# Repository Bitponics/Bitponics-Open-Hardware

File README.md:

### Hardware
- Bitponics board
- [FTDI adapter](http://www.amazon.com/FTDI-Basic-Breakout-5V/dp/B0068QKQEA/ref=sr_1_5?ie=UTF8&qid=1372819998&sr=8-5&keywords=ftdi)
- Mini USB cable

### Software
- [Arduino 1.0.1](http://arduino.cc/en/Main/Software)
- [FTDI driver](http://www.ftdichip.com/Drivers/VCP.htm)

### Setup
- Copy all directories from `./libraries` into your Arduino's global `libraries` folder. (Usually ~/Documents/Arduino/libraries)
- Open Bitponics code in Arduino
- Set board to "Arduino 2560"
- Set serial your usb serial port
- upload firmware

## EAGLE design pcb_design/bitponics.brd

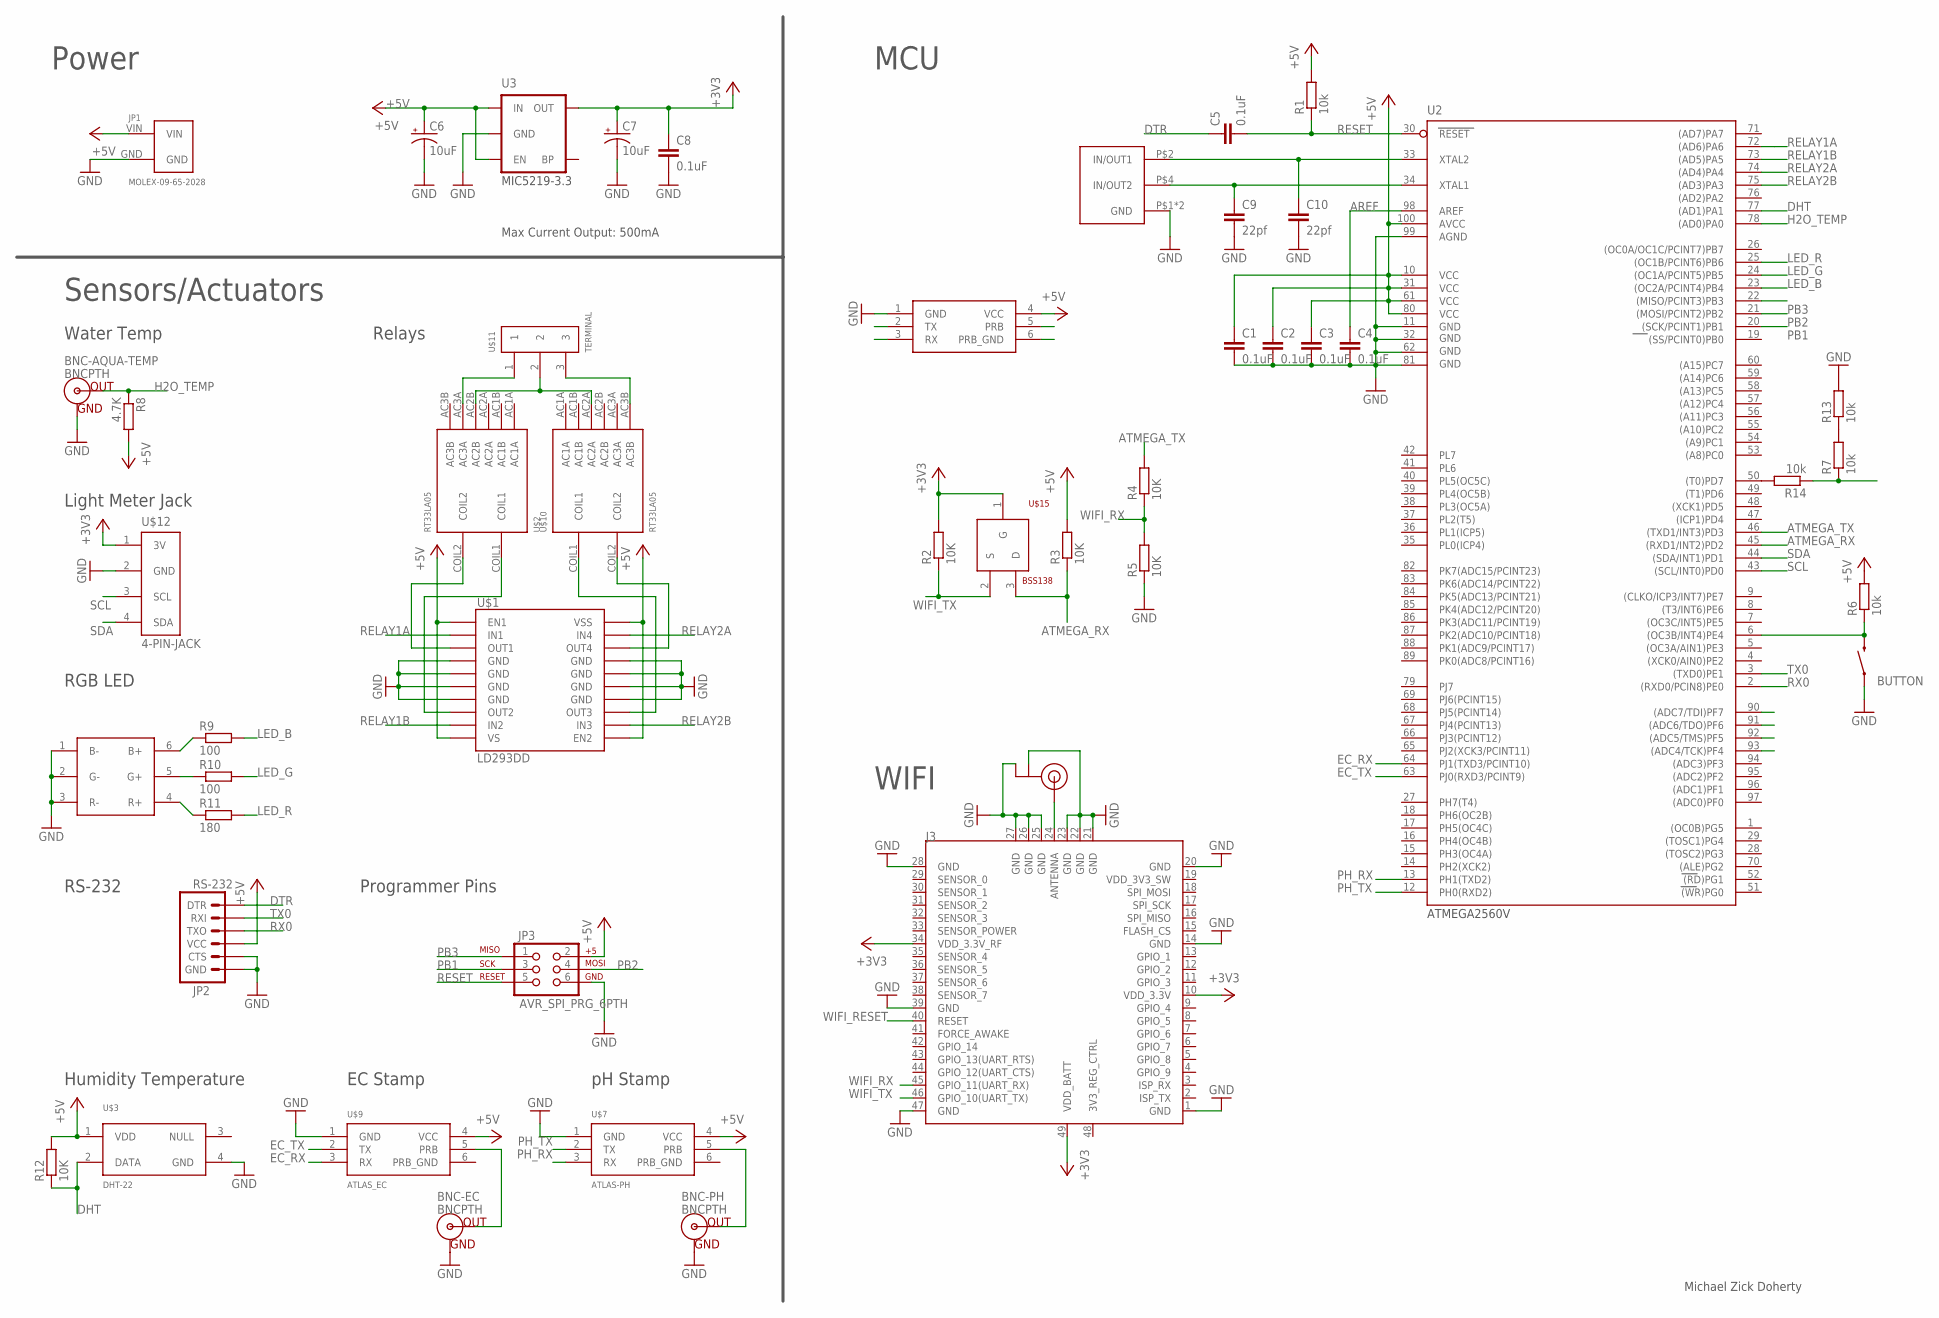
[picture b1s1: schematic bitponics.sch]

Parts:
BNC-AQUA-TEMP: BNCPTH; BNC
BNC-EC: BNCPTH; BNC
BNC-PH: BNCPTH; BNC
BUTTON: FSMRA2JH
C1, C2, C3, C4, C5, C8: 0.1uF; C0603
C6, C7: 10uF; EIA3216
C9, C10: 22pf; C0603
J3: WIFI-RN-171; 49P-1.27-26.67X17.78
JP1: MOLEX-09-65-2028; 09-65-2028
JP2: RS-232; 1X06_LOCK
JP3: AVR_SPI_PRG_6PTH; 2X3
R1, R6, R7, R13, R14: 10k; R0603
R2, R3, R4, R5, R12: 10K; R0603
R8: 4.7K; R0603
R9, R10: 100; R0603
R11: 180; R0603
U2: ATMEGA2560AU; TQFP100
U3: V_REG_LDOSMD; SOT23-5
U13: RGB-LED
U$1: LD293DD; SO-20LD
U$2, U$10: RT33LA05
U$3: DHT-22; DHT22
U$4, U$7: ATLAS-PH; PH
U$5: U.FL
U$6: ECX-32
U$9: ATLAS_EC; EC
U$11: TERMINAL
U$12: 4-PIN-JACK
U$15: BSS138; SOT23

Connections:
+3V3: C7.A (+), C8.1, J3.10 (VDD_3.3V), J3.34 (VDD_3.3V_RF), J3.49 (VDD_BATT), R2.2, U3.5 (OUT), U$12.1 (3V), U$15.1 (G)
+5V: C1.1, C2.1, C3.1, C6.A (+), JP1.VIN, JP2.4 (VCC), JP3.2, R1.2, R3.2, R6.2, R8.2, R12.2, U2.10 (VCC), U2.31 (VCC1), U2.61 (VCC2), U2.80 (VCC3), U2.100 (AVCC), U3.1 (IN), U3.3 (EN), U$1.1 (EN1), U$1.10 (VS), U$1.11 (EN2), U$1.20 (VSS), U$3.1 (VDD), U$4.4 (VCC), U$7.4 (VCC), U$9.4 (VCC)
A4: U2.93 ((ADC4/TCK)PF4), U$4.5 (PRB)
A5: U2.92 ((ADC5/TMS)PF5), U$4.6 (PRB_GND)
A6: U2.91 ((ADC6/TDO)PF6), U$4.3 (RX)
A7: U2.90 ((ADC7/TDI)PF7), U$4.2 (TX)
AREF: C4.1, U2.98 (AREF)
ATMEGA_RX: R3.1, U2.45 ((RXD1/INT2)PD2), U$15.3 (D)
ATMEGA_TX: R4.2, U2.46 ((TXD1/INT3)PD3)
DHT: R12.1, U2.77 ((AD1)PA1), U$3.2 (DATA)
DTR: C5.1, JP2.1 (DTR)
EC_RX: U2.64 (PJ1(TXD3/PCINT10)), U$9.3 (RX)
EC_TX: U2.63 (PJ0(RXD3/PCINT9)), U$9.2 (TX)
GND: BNC-AQUA-TEMP.GND, BNC-EC.GND, BNC-PH.GND, BUTTON.2A (1), C1.2, C2.2, C3.2, C4.2, C6.C (-), C7.C (-), C8.2, C9.2, C10.2, J3.1 (GND), J3.14 (GND), J3.20 (GND), J3.21 (GND), J3.22 (GND), J3.23 (GND), J3.25 (GND), J3.26 (GND), J3.27 (GND), J3.28 (GND), J3.39 (GND), J3.47 (GND), JP1.GND, JP2.5 (CTS), JP2.6 (GND), JP3.6, R5.1, R13.2, U2.11 (GND), U2.32 (GND1), U2.62 (GND2), U2.81 (GND3), U2.99 (AGND), U3.2 (GND), U13.1 (B-), U13.2 (G-), U13.3 (R-), U$1.4 (GND), U$1.5 (GND), U$1.6 (GND), U$1.7 (GND), U$1.14 (GND), U$1.15 (GND), U$1.16 (GND), U$1.17 (GND), U$3.4 (GND), U$4.1 (GND), U$5.P$1 (GND), U$5.P$2 (GND), U$6.P$1 (GND), U$6.P$3 (GND), U$7.1 (GND), U$9.1 (GND), U$12.2 (GND)
H2O_TEMP: BNC-AQUA-TEMP.S (OUT), R8.1, U2.78 ((AD0)PA0)
LED_B: R9.2, U2.23 ((OC2A/PCINT4)PB4)
LED_G: R10.2, U2.24 ((OC1A/PCINT5)PB5)
LED_R: R11.2, U2.25 ((OC1B/PCINT6)PB6)
unnamed: BNC-EC.S (OUT), U$9.5 (PRB)
unnamed: BNC-PH.S (OUT), U$7.5 (PRB)
unnamed: U$1.13 (OUT3), U$10.COIL1
unnamed: U$2.AC3A, U$11.1
unnamed: U$2.AC2B, U$10.AC2A, U$11.2
unnamed: U$10.AC3B, U$11.3
unnamed: C10.1, U2.33 (XTAL2), U$6.P$2 (IN/OUT1)
unnamed: U$1.18 (OUT4), U$10.COIL2
unnamed: R10.1, U13.5 (G+)
unnamed: R11.1, U13.4 (R+)
unnamed: R9.1, U13.6 (B+)
unnamed: C9.1, U2.34 (XTAL1), U$6.P$4 (IN/OUT2)
unnamed: J3.24 (ANTENNA), U$5.P$3 (SIGNAL)
unnamed: U$1.3 (OUT1), U$2.COIL2
unnamed: U$1.8 (OUT2), U$2.COIL1
unnamed: R7.2, R13.1
unnamed: R14.2, U2.50 ((T0)PD7)
unnamed: BUTTON.2B (2), R6.1, U2.6 ((OC3B/INT4)PE4)
PB1: JP3.3, U2.20 ((SCK/PCINT1)PB1)
PB2: JP3.4, U2.21 ((MOSI/PCINT2)PB2)
PB3: JP3.1, U2.22 ((MISO/PCINT3)PB3)
PH_RX: U2.13 (PH1(TXD2)), U$7.3 (RX)
PH_TX: U2.12 (PH0(RXD2)), U$7.2 (TX)
RELAY1A: U2.72 ((AD6)PA6), U$1.2 (IN1)
RELAY1B: U2.73 ((AD5)PA5), U$1.9 (IN2)
RELAY2A: U2.74 ((AD4)PA4), U$1.19 (IN4)
RELAY2B: U2.75 ((AD3)PA3), U$1.12 (IN3)
RESET: C5.2, JP3.5, R1.1, U2.30 (RESET)
RX0: JP2.3 (TXO), U2.2 ((RXD0/PCIN8)PE0)
SCL: U2.43 ((SCL/INT0)PD0), U$12.3 (SCL)
SDA: U2.44 ((SDA/INT1)PD1), U$12.4 (SDA)
TX0: JP2.2 (RXI), U2.3 ((TXD0)PE1)
WIFI_RESET: J3.40 (RESET), R7.1, R14.1
WIFI_RX: J3.45 (GPIO_11(UART_RX)), R4.1, R5.2
WIFI_TX: J3.46 (GPIO_10(UART_TX)), R2.1, U$15.2 (S)

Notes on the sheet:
Sensors/Actuators
Power
MCU
MIC5219-3.3
ATMEGA2560V
Max Current Output: 500mA
Michael Zick Doherty
Programmer Pins
RS-232
Water Temp
RGB LED
Humidity Temperature
EC Stamp
pH Stamp
WIFI
Relays
Light Meter Jack

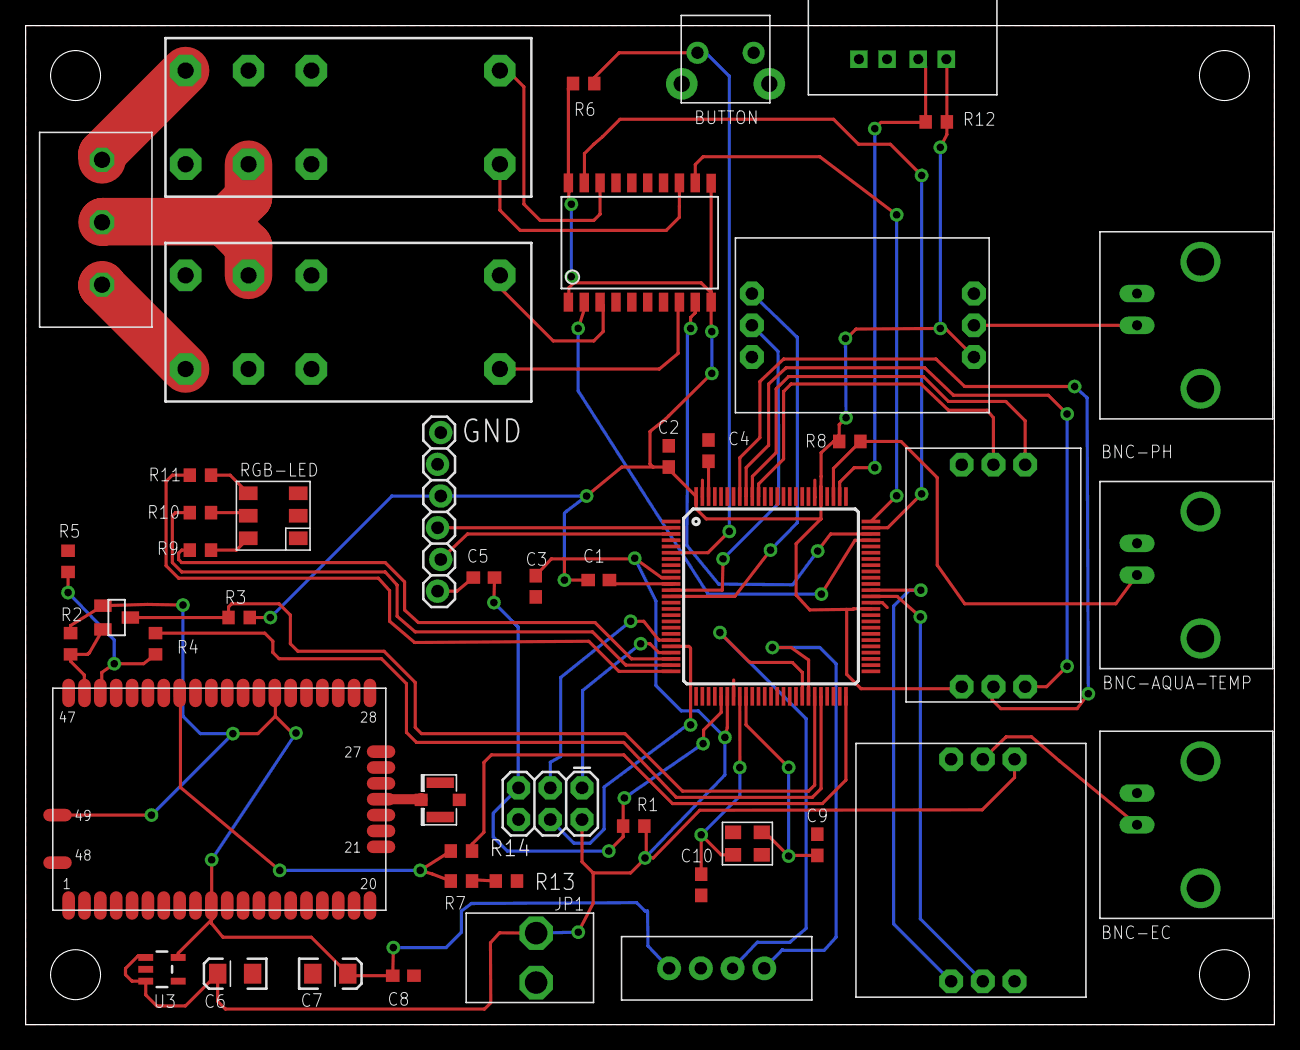
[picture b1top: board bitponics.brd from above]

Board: 2 copper layers, 100.0 x 80.0 mm, 47 parts (0 on the bottom side), 53 nets.

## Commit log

2012-09-20 Typo Fix & Adding Wifi Connection
2012-09-20 Remove typo
2012-09-20 Associated Request Handler cyles & refresh checking
2012-09-21 Added Light Data, Temp Data, Fert Auth, Custom Datatypes
2012-09-21 Added Ec,PH & Json Call to sensor_logs
2012-09-21 poll sensor_logs & refresh_status
2012-09-21 Initial Add
2012-09-21 Wait for server response before making a call
2012-09-22 Adding Overrides & memory checks
2012-09-22 Added EEPROM read and write reset
2012-09-22 Adding
2012-09-22 updating/cleaning up
2013-02-10 - consolidated logic on when to enter Wifi Adhoc mode into single file (wifi.ino) - in keeping with "method names should be verbs" rule, renamed wifiAssociated() to associateWifi() - changed associat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
2013-02-10 added our fork of WiFlyHQ as a submodule
2013-02-13 nesting dependencies within the /lib folder. for the ones i could find on github, added as git submodules
2013-02-13 changed lib references to reference the local versions & rolled back my wifi logic refactoring from a couple commits ago
2013-02-13 rolled back to referencing external libs & reapplied wifi refactoring
2013-03-16 wifi ap mode
2013-03-19 Wifi connection finessing
2013-03-20 Fixed AP connection, AP Request Headers fixed GET & POST checking
2013-03-25 Keeping Current
2013-03-25 more setup instructions for README
2013-03-25 deleting all git submodules; they weren't the right versions
2013-03-25 copying all of Chris P's libraries into the repo, renaming lib to libraries to be more consistent with Arduino environment
2013-03-25 deleting external .git refs from libraries and recommitting. will refactor into using submodules later
2013-03-31 LED function, WDT reset function, new lux library
2013-03-31 swapped lux lib
2013-05-11 updated routines
2013-05-14 new device protocol
2013-05-15 streamline calibration flow
2013-05-26 updated relay triggering
2013-08-07 new protocol
2013-08-20 Rename bitponics_fw.ino to bitponics_firmware.ino
2013-08-20 cleaned up debugging code
2013-08-24 updates baud rate
2013-09-08 updated protocol for getting EC values
2013-09-08 wifi firmware update check
2013-09-26 Fix for reset button
2013-10-07 Fix calibration flow, updated for latest version of Arduino IDE
2013-10-07 limit serial logging
2013-10-09 updating AP mode network name to be more descriptive
2013-10-18 multiple networks scans
2013-10-18 Updates to network scanning
2013-11-09 reworked wifi association
2013-12-03 -updated wifi association flow
2014-01-10 implemented reset circuit
2014-01-16 fixed bug with wifi scan, optimized calibration
2014-02-05 updated timings on calibration
2014-02-06 ping
2014-02-12 adding pcb design files + reorganizing

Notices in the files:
parts and their libraries:
SparkFun-Connectors: Licensing: CC v3.0 Share-Alike You are welcome to use this library for commercial purposes.
